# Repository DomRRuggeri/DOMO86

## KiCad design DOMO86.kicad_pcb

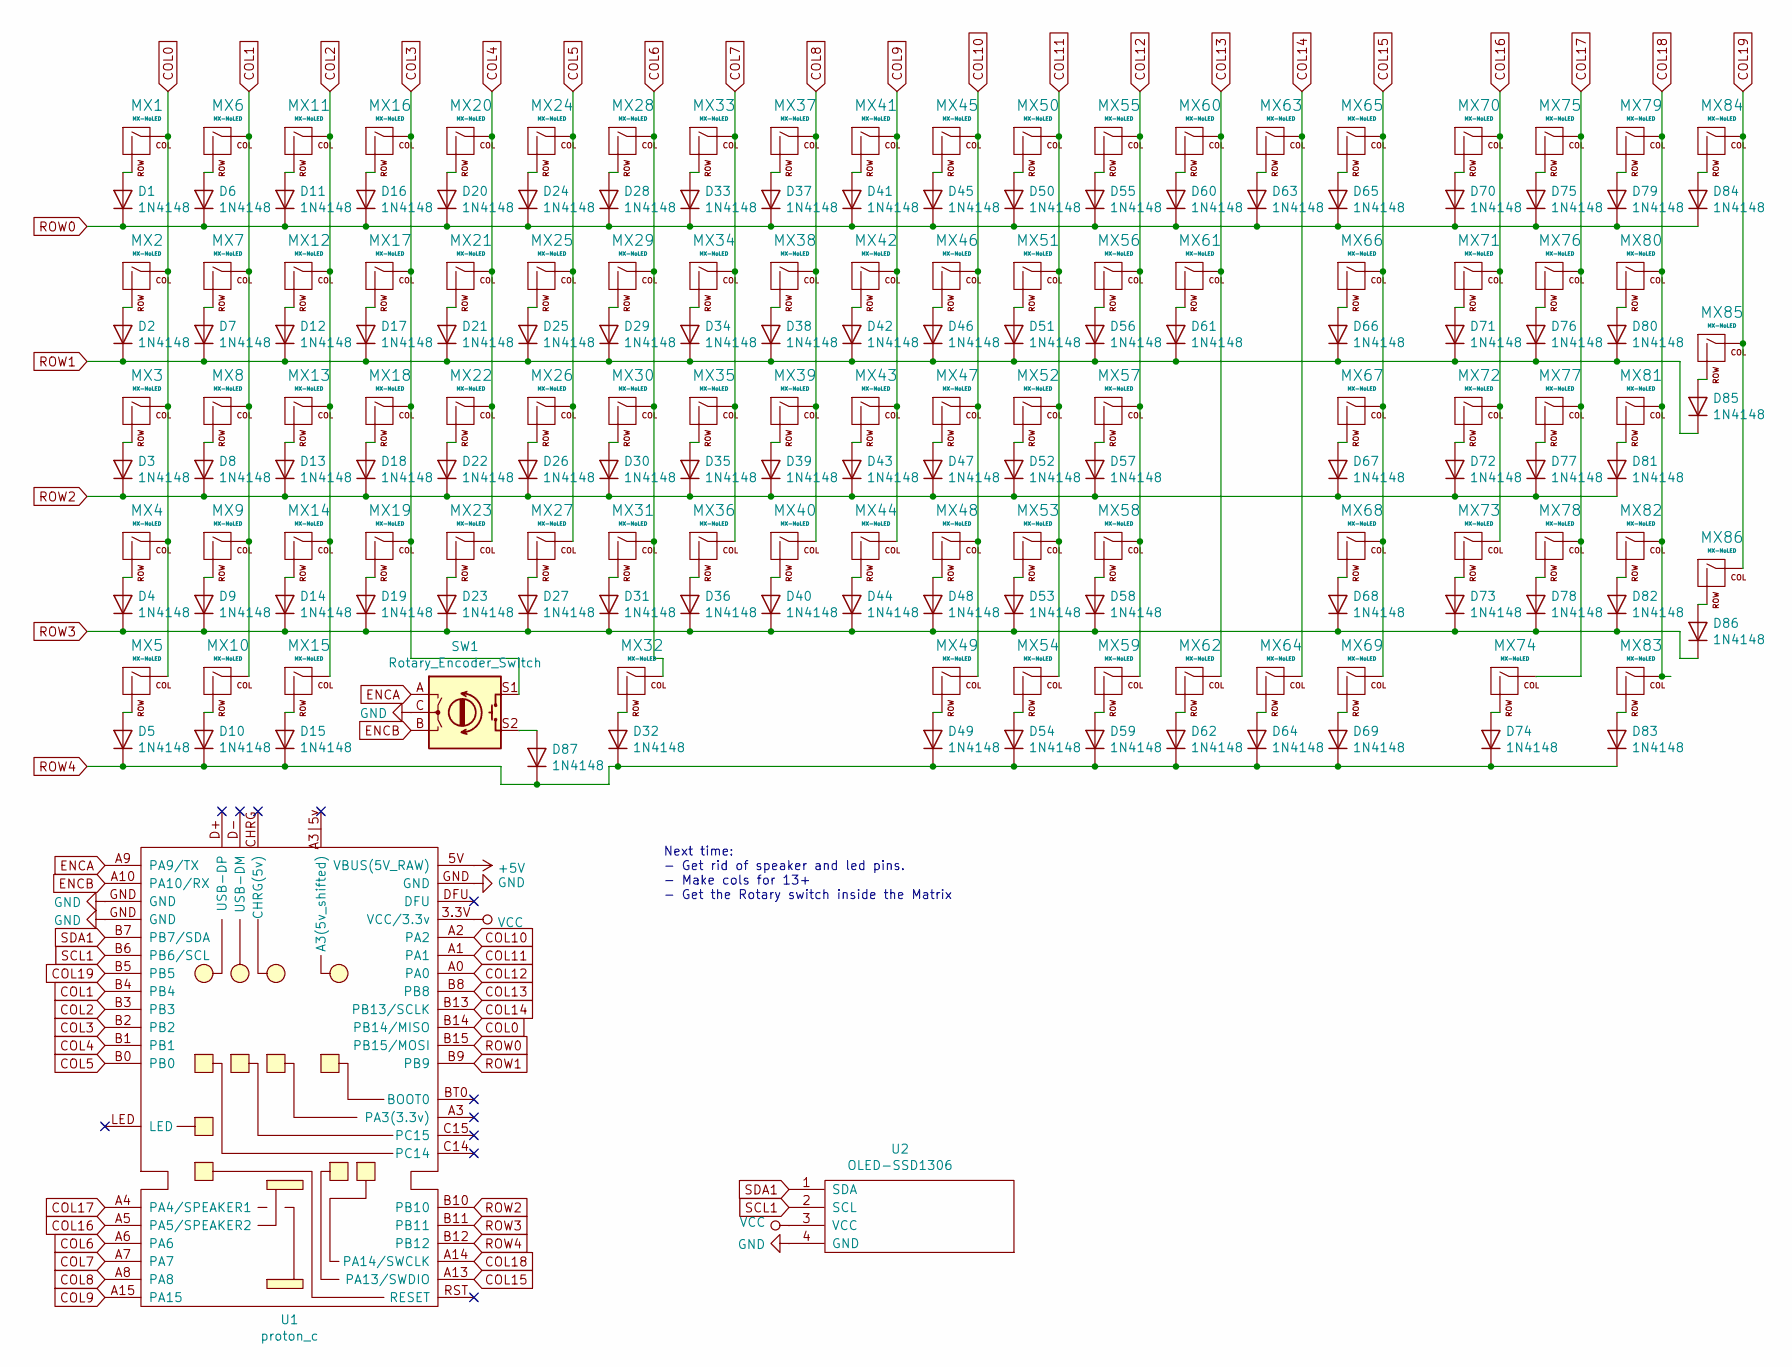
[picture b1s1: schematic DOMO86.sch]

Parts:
D1, D2, D3, D4, D5, D6, D7, D8, D9, D10, D11, D12, D13, D14, D15, D16, D17, D18, D19, D20, D21, D22, D23, D24, D25, D26, D27, D28, D29, D30, D31, D32, D33, D34, D35, D36, D37, D38, D39, D40, D41, D42, D43, D44, D45, D46, D47, D48, D49, D50, D51, D52, D53, D54, D55, D56, D57, D58, D59, D60, D61, D62, D63, D64, D65, D66, D67, D68, D69, D70, D71, D72, D73, D74, D75, D76, D77, D78, D79, D80, D81, D82, D83, D84, D85, D86, D87: 1N4148; D_DO-35_SOD27_P5.08mm_Horizontal
MX1, MX6, MX7, MX8, MX9, MX11, MX12, MX13, MX14, MX16, MX17, MX18, MX19, MX20, MX21, MX22, MX23, MX24, MX25, MX26, MX27, MX28, MX29, MX30, MX31, MX33, MX34, MX35, MX36, MX37, MX38, MX39, MX40, MX41, MX42, MX43, MX44, MX45, MX46, MX47, MX48, MX49, MX50, MX51, MX52, MX54, MX55, MX56, MX58, MX59, MX60, MX62, MX63, MX64, MX65, MX66, MX67, MX68, MX69, MX70, MX71, MX72, MX73, MX75, MX76, MX77, MX78, MX79, MX80, MX81, MX82, MX83, MX84: MX-NoLED; MXOnly-1U-NoLED
MX2, MX61: MX-NoLED; MXOnly-1.5U-NoLED
MX3, MX53: MX-NoLED; MXOnly-1.75U-NoLED
MX4, MX57: MX-NoLED; MXOnly-2.25U-NoLED
MX5, MX10, MX15: MX-NoLED; MXOnly-1.25U-NoLED
MX32: MX-NoLED; MXOnly-6.25U-ReversedStabilizers-NoLED
MX74: MX-NoLED; MXOnly-2U-ReversedStabilizers-NoLED
MX85, MX86: MX-NoLED; MXOnly-2U-NoLED
SW1: Rotary_Encoder_Switch; RotaryEncoder_Alps_EC11E-Switch_Vertical_H20mm
U1: proton_c
U2: OLED-SSD1306; OLED-1306

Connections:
+5V: U1.5V (VBUS(5V_RAW))
COL0: MX1.1 (COL), MX2.1 (COL), MX3.1 (COL), MX4.1 (COL), MX5.1 (COL), U1.B14 (PB14/MISO)
COL1: MX6.1 (COL), MX7.1 (COL), MX8.1 (COL), MX9.1 (COL), MX10.1 (COL), U1.B4
COL2: MX11.1 (COL), MX12.1 (COL), MX13.1 (COL), MX14.1 (COL), MX15.1 (COL), U1.B3
COL3: MX16.1 (COL), MX17.1 (COL), MX18.1 (COL), MX19.1 (COL), SW1.S1, U1.B2
COL4: MX20.1 (COL), MX21.1 (COL), MX22.1 (COL), MX23.1 (COL), U1.B1
COL5: MX24.1 (COL), MX25.1 (COL), MX26.1 (COL), MX27.1 (COL), U1.B0
COL6: MX28.1 (COL), MX29.1 (COL), MX30.1 (COL), MX31.1 (COL), MX32.1 (COL), U1.A6
COL7: MX33.1 (COL), MX34.1 (COL), MX35.1 (COL), MX36.1 (COL), U1.A7
COL8: MX37.1 (COL), MX38.1 (COL), MX39.1 (COL), MX40.1 (COL), U1.A8
COL9: MX41.1 (COL), MX42.1 (COL), MX43.1 (COL), MX44.1 (COL), U1.A15
COL10: MX45.1 (COL), MX46.1 (COL), MX47.1 (COL), MX48.1 (COL), MX49.1 (COL), U1.A2
COL11: MX50.1 (COL), MX51.1 (COL), MX52.1 (COL), MX53.1 (COL), MX54.1 (COL), U1.A1
COL12: MX55.1 (COL), MX56.1 (COL), MX57.1 (COL), MX58.1 (COL), MX59.1 (COL), U1.A0
COL13: MX60.1 (COL), MX61.1 (COL), MX62.1 (COL), U1.B8
COL14: MX63.1 (COL), MX64.1 (COL), U1.B13 (PB13/SCLK)
COL15: MX65.1 (COL), MX66.1 (COL), MX67.1 (COL), MX68.1 (COL), MX69.1 (COL), U1.A13 (PA13/SWDIO)
COL16: MX70.1 (COL), MX71.1 (COL), MX72.1 (COL), MX73.1 (COL), U1.A5 (PA5/SPEAKER2)
COL17: MX74.1 (COL), MX75.1 (COL), MX76.1 (COL), MX77.1 (COL), MX78.1 (COL), U1.A4 (PA4/SPEAKER1)
COL18: MX79.1 (COL), MX80.1 (COL), MX81.1 (COL), MX82.1 (COL), MX83.1 (COL), U1.A14 (PA14/SWCLK)
COL19: MX84.1 (COL), MX85.1 (COL), MX86.1 (COL), U1.B5
ENCA: SW1.A, U1.A9 (PA9/TX)
ENCB: SW1.B, U1.A10 (PA10/RX)
GND: SW1.C, U1.GND, U2.4 (GND)
unnamed: D1.2 (A), MX1.2 (ROW)
unnamed: D2.2 (A), MX2.2 (ROW)
unnamed: D3.2 (A), MX3.2 (ROW)
unnamed: D4.2 (A), MX4.2 (ROW)
unnamed: D5.2 (A), MX5.2 (ROW)
unnamed: D6.2 (A), MX6.2 (ROW)
unnamed: D7.2 (A), MX7.2 (ROW)
unnamed: D8.2 (A), MX8.2 (ROW)
unnamed: D9.2 (A), MX9.2 (ROW)
unnamed: D10.2 (A), MX10.2 (ROW)
unnamed: D11.2 (A), MX11.2 (ROW)
unnamed: D12.2 (A), MX12.2 (ROW)
unnamed: D13.2 (A), MX13.2 (ROW)
unnamed: D14.2 (A), MX14.2 (ROW)
unnamed: D15.2 (A), MX15.2 (ROW)
unnamed: D16.2 (A), MX16.2 (ROW)
unnamed: D17.2 (A), MX17.2 (ROW)
unnamed: D18.2 (A), MX18.2 (ROW)
unnamed: D19.2 (A), MX19.2 (ROW)
unnamed: D20.2 (A), MX20.2 (ROW)
unnamed: D21.2 (A), MX21.2 (ROW)
unnamed: D22.2 (A), MX22.2 (ROW)
unnamed: D23.2 (A), MX23.2 (ROW)
unnamed: D24.2 (A), MX24.2 (ROW)
unnamed: D25.2 (A), MX25.2 (ROW)
unnamed: D26.2 (A), MX26.2 (ROW)
unnamed: D27.2 (A), MX27.2 (ROW)
unnamed: D28.2 (A), MX28.2 (ROW)
unnamed: D29.2 (A), MX29.2 (ROW)
unnamed: D30.2 (A), MX30.2 (ROW)
unnamed: D31.2 (A), MX31.2 (ROW)
unnamed: D32.2 (A), MX32.2 (ROW)
unnamed: D33.2 (A), MX33.2 (ROW)
unnamed: D34.2 (A), MX34.2 (ROW)
unnamed: D35.2 (A), MX35.2 (ROW)
unnamed: D36.2 (A), MX36.2 (ROW)
unnamed: D37.2 (A), MX37.2 (ROW)
unnamed: D38.2 (A), MX38.2 (ROW)
unnamed: D39.2 (A), MX39.2 (ROW)
unnamed: D40.2 (A), MX40.2 (ROW)
unnamed: D41.2 (A), MX41.2 (ROW)
unnamed: D42.2 (A), MX42.2 (ROW)
unnamed: D43.2 (A), MX43.2 (ROW)
unnamed: D44.2 (A), MX44.2 (ROW)
unnamed: D45.2 (A), MX45.2 (ROW)
unnamed: D46.2 (A), MX46.2 (ROW)
unnamed: D47.2 (A), MX47.2 (ROW)
unnamed: D48.2 (A), MX48.2 (ROW)
unnamed: D49.2 (A), MX49.2 (ROW)
unnamed: D50.2 (A), MX50.2 (ROW)
unnamed: D51.2 (A), MX51.2 (ROW)
unnamed: D52.2 (A), MX52.2 (ROW)
unnamed: D53.2 (A), MX53.2 (ROW)
unnamed: D54.2 (A), MX54.2 (ROW)
unnamed: D55.2 (A), MX55.2 (ROW)
unnamed: D56.2 (A), MX56.2 (ROW)
unnamed: D57.2 (A), MX57.2 (ROW)
unnamed: D58.2 (A), MX58.2 (ROW)
unnamed: D59.2 (A), MX59.2 (ROW)
unnamed: D60.2 (A), MX60.2 (ROW)
unnamed: D61.2 (A), MX61.2 (ROW)
unnamed: D62.2 (A), MX62.2 (ROW)
unnamed: D63.2 (A), MX63.2 (ROW)
unnamed: D64.2 (A), MX64.2 (ROW)
unnamed: D65.2 (A), MX65.2 (ROW)
unnamed: D66.2 (A), MX66.2 (ROW)
unnamed: D67.2 (A), MX67.2 (ROW)
unnamed: D68.2 (A), MX68.2 (ROW)
unnamed: D69.2 (A), MX69.2 (ROW)
unnamed: D70.2 (A), MX70.2 (ROW)
unnamed: D71.2 (A), MX71.2 (ROW)
unnamed: D72.2 (A), MX72.2 (ROW)
unnamed: D73.2 (A), MX73.2 (ROW)
unnamed: D74.2 (A), MX74.2 (ROW)
unnamed: D75.2 (A), MX75.2 (ROW)
unnamed: D76.2 (A), MX76.2 (ROW)
unnamed: D77.2 (A), MX77.2 (ROW)
unnamed: D78.2 (A), MX78.2 (ROW)
unnamed: D79.2 (A), MX79.2 (ROW)
unnamed: D80.2 (A), MX80.2 (ROW)
unnamed: D81.2 (A), MX81.2 (ROW)
unnamed: D82.2 (A), MX82.2 (ROW)
unnamed: D83.2 (A), MX83.2 (ROW)
unnamed: D84.2 (A), MX84.2 (ROW)
unnamed: D85.2 (A), MX85.2 (ROW)
unnamed: D86.2 (A), MX86.2 (ROW)
unnamed: D87.2 (A), SW1.S2
ROW0: D1.1 (K), D6.1 (K), D11.1 (K), D16.1 (K), D20.1 (K), D24.1 (K), D28.1 (K), D33.1 (K), D37.1 (K), D41.1 (K), D45.1 (K), D50.1 (K), D55.1 (K), D60.1 (K), D63.1 (K), D65.1 (K), D70.1 (K), D75.1 (K), D79.1 (K), D84.1 (K), U1.B15 (PB15/MOSI)
ROW1: D2.1 (K), D7.1 (K), D12.1 (K), D17.1 (K), D21.1 (K), D25.1 (K), D29.1 (K), D34.1 (K), D38.1 (K), D42.1 (K), D46.1 (K), D51.1 (K), D56.1 (K), D61.1 (K), D66.1 (K), D71.1 (K), D76.1 (K), D80.1 (K), D85.1 (K), U1.B9
ROW2: D3.1 (K), D8.1 (K), D13.1 (K), D18.1 (K), D22.1 (K), D26.1 (K), D30.1 (K), D35.1 (K), D39.1 (K), D43.1 (K), D47.1 (K), D52.1 (K), D57.1 (K), D67.1 (K), D72.1 (K), D77.1 (K), D81.1 (K), U1.B10
ROW3: D4.1 (K), D9.1 (K), D14.1 (K), D19.1 (K), D23.1 (K), D27.1 (K), D31.1 (K), D36.1 (K), D40.1 (K), D44.1 (K), D48.1 (K), D53.1 (K), D58.1 (K), D68.1 (K), D73.1 (K), D78.1 (K), D82.1 (K), D86.1 (K), U1.B11
ROW4: D5.1 (K), D10.1 (K), D15.1 (K), D32.1 (K), D49.1 (K), D54.1 (K), D59.1 (K), D62.1 (K), D64.1 (K), D69.1 (K), D74.1 (K), D83.1 (K), D87.1 (K), U1.B12
SCL1: U1.B6 (PB6/SCL), U2.2 (SCL)
SDA1: U1.B7 (PB7/SDA), U2.1 (SDA)
VCC: U1.3.3V (VCC/3.3v), U2.3 (VCC)

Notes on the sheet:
Next time: - Get rid of speaker and led pins. - Make cols for 13+ - Get the Rotary switch inside the Matrix

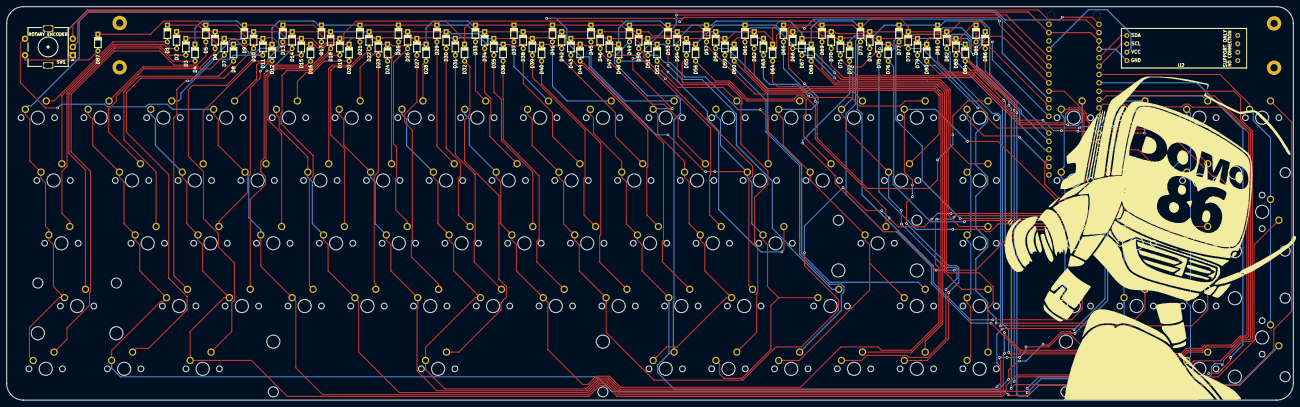
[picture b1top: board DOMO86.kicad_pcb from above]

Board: 2 copper layers, 390.4 x 119.4 mm, 176 parts (1 on the bottom side), 118 nets.

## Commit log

2019-12-03 initial
2019-12-03 Added submodules
2019-12-03 Added footprint libraries
2019-12-05 Did a bunch of things- created footprint for oled ssd1306
2019-12-09 Went from 0 to 100 real quick.
2019-12-09 Pushing before all track delete.
2019-12-11 Finished routing
2019-12-12 Added rows/cols, cleared edges
2019-12-12 Moved a trace
2019-12-12 Saving before diode/track redo
